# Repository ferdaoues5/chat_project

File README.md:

# Projet ESE  — Robot chat/souris

## Résumé 
Le but du projet est de concevoir un robot capable de se déplacer sur une table (sans tomber de la table), évitant les obstacles, et détectant les autres robots se trouvant sur la table. 
Le robot se trouvant avec d'autres robots sur la table joue soit le rôle de chat ou soit le rôle de souris (jeu du chat et de la souris).

Une liste de composants nous a été imposée.

## 1. Schéma architectural de notre robot

**Liste du matériel**

On utilise le microcontroleur STM32G070RBT6 pour récupérer les données provenants des capteurs, commander les moteurs...

| Capteurs  | Actionneurs | IHM | Horloge |
| ------------- | ------------- | ------------- | ------------- |
| Détection des autres robots : YDLIDAR X4  | 2 Drivers moteurs : ZXBM5210-S | Interrupteur ON/OFF| Quartz 16 MHz |
| Capteurs de bordure (table) : Sharp GP2Y0D805Z0F  | 2 moteurs : DfRobot FIT0520 ou FIT0521 | LEDs indicatives du rôle (chat ou souris)  |  |
| Bumpers (détection de collision)  | | Led de débogage |  |
|Encodeur (pour mesurer vitesse moteur il me semble) | | |  |

## Deadlines

**Entre la toussaint et noel**

- Bibliothèques logicielles
- Drivers
- Organisation du code
- Stratégie et comportements
  
Vacances noel : Samedi 23 décembre au Dimanche 7 janvier  

**Après noel**  
Dernière séance : stratégie et comportements  
TP d’Introduction à la robotique  

**Challenge** le vendredi 12 janvier

Fin du semestre : Samedi 13 janvier  

## Objectifs restants 
**23/11/2023** On a fini le PCB, soudé tous les composants qu'il fallait. Il nous reste maintenant à nous occuper de l'architecture logicielle dans le microcontroleur.
1 niveau d'objectifs au minimum doit être accompli par semaine.

**Niveau 0 :**
Le robot se déplace,
Il ne tombe pas de la table.

**Niveau 1 :**
Il détecte et se dirige vers un objet,
Ou s’en éloigne s’il n’est pas le chat.

**Niveau 2 :**
Il change de comportement (proie/prédateur) après un contact,
Il fonctionne avec plusieurs robots sur la table.

**Niveau 3 :**
Il n’est pas affecté par les obstacles hors de la table,
Il est donc capable de se localiser.

## Problèmes rencontrés

### - Mauvaise liaison du 5V entre la broche du Lidar et un autre point du circuit censé recevoir 5V aussi

__Résolution du problème__ : en soudant un câble entre ces deux points.

### - Pas de capteurs réfléchissants pour la bordure (Sharp GP2Y0D805Z0F)

Il n'y avait plus de capteurs réfléchissants. Heureusement, on nous a suggeré d'utiliser les switchs, et cela est fonctionnel. En fait le robot quand il est sur la table, la languette est près du switch vu que le sol exerce une force vers le haut sur la languette du switch. On a cablé le switch de sorte à ce qu'il soit "normally opened" et donc qu'il transmette une tension que quand la languette s'ouvre.

### - Le contrôle des moteurs
On était tellement tous concentrés sur l'aspect de programmation qu'on en a oublié de tester le bon fonctionnement des composants de notre carte. Résultat, on s'est rendu compte bien trop tard qu'on ne pouvait pas générer de la PWM sur les broches du microcontroleurs reliées aux drivers. Du coup, on ne pouvait seulement contrôler les moteurs en tout ou rien. Il aurait fallu prévoir de mettre une PWM sur Vref des drivers comme ça on aurait été capable de contrôler la vitesse des moteurs dans le cas où la PWM ne serait pas générée pour les entrées du driver. Le problème n'était pas software puisqu'on a réussi à générer de la PWM sur d'autres broches (ex : celle qui était reliée à la broche M_SCTR du LIDAR). On a même essayé de voir à l'oscillo si on avait de la PWM directement sur les broches du STM32. A un moment, une PWM est soudainement apparu sur la broche FWD du driver, puis elle a disparue. 

### - Le Lidar
Un coup, lors du scan, le lidar ne nous donnait pas les 2 octets marquant le début de la trame (0xA55A), un coup il faisait. C'est quelque chose que je ne comprenais. Finalement, le problème venait peut-être du fait d'utiliser l'alimentation continue bleue car bizarrement quand on utilisait la batterie 7.2V NiMH on avait plus de problème de perturbation de la tension et on arrivait à obtenir une trame correcte.

Pas trop de problèmes rencontrés pour la commande health check.

## Au final...

Le robot peut effectivemment "se déplacer" mais comme il le fait à toute vitesse : à cause de son inertie, quand le capteur de bordure lui enverra l'info comme quoi il y a du vide, il tombera dans le vide, même s'il s'arrête.

## Leçons à tirer

- Tester tous les composants et s'assurer de leur bon fonctionnement avant de passer à la partie software
- Mieux communiquer et bien répartir le travail
- Discuter davantage avec d'autres élèves lorsque l'on rencontre des problèmes pour savoir si eux aussi on rencontré les mêmes problèmes

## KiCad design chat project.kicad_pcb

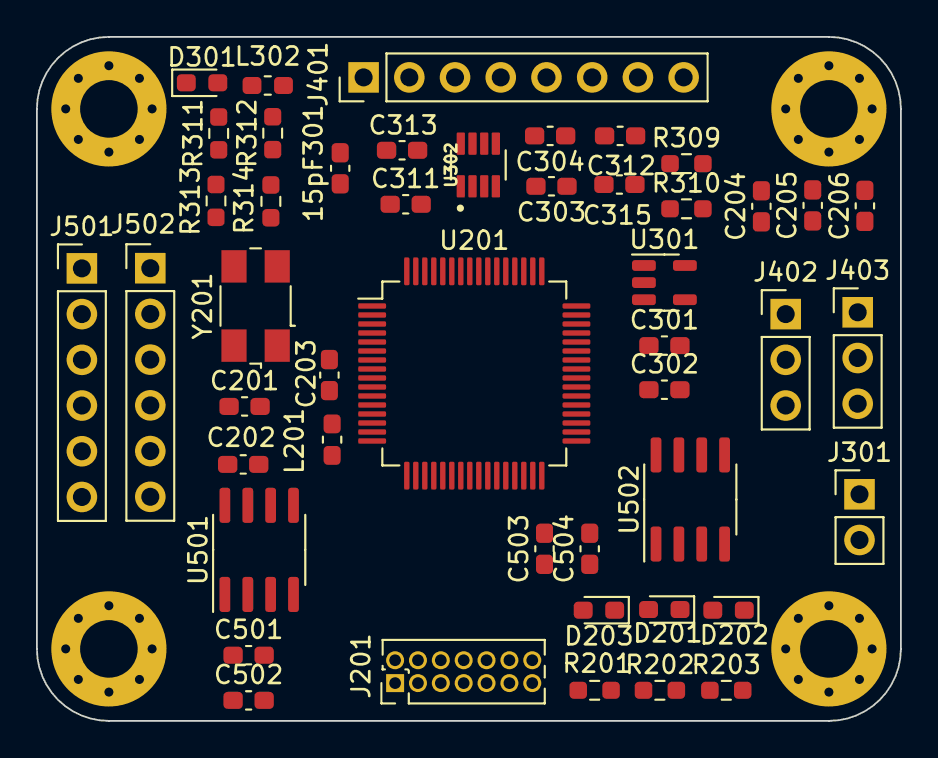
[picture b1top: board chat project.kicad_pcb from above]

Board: 4 copper layers, 48.0 x 38.0 mm, 51 parts (0 on the bottom side), 46 nets, no tracks yet.

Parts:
15pF301: C_Small; C_0603_1608Metric_Pad1.08x0.95mm_HandSolder
C201, C202: 10pF; C_0603_1608Metric_Pad1.08x0.95mm_HandSolder
C203, C301, C302: 1uF; C_0603_1608Metric_Pad1.08x0.95mm_HandSolder
C204, C205: 100nF; C_0603_1608Metric_Pad1.08x0.95mm_HandSolder
C206: 4.7uF; C_0603_1608Metric_Pad1.08x0.95mm_HandSolder
C303, C311, C315: 0.1uF; C_0603_1608Metric_Pad1.08x0.95mm_HandSolder
C304, C312, C313: 22uF; C_0603_1608Metric_Pad1.08x0.95mm_HandSolder
C501, C503: 1µF; C_0603_1608Metric_Pad1.08x0.95mm_HandSolder
C502, C504: 10µF; C_0603_1608Metric_Pad1.08x0.95mm_HandSolder
D201, D202: LED; LED_0603_1608Metric_Pad1.05x0.95mm_HandSolder
D203: RED; LED_0603_1608Metric_Pad1.05x0.95mm_HandSolder
D301: D; D_0603_1608Metric_Pad1.05x0.95mm_HandSolder
H101, H102, H103, H104: MountingHole_Pad; MountingHole_3.2mm_M3_Pad_Via
J201: Conn_02x07_Odd_Even; PinHeader_2x07_P1.27mm_Vertical
J301: Conn_01x02; PinHeader_1x02_P2.54mm_Vertical
J401: Conn_01x08; PinHeader_1x08_P2.54mm_Vertical
J402, J403: Conn_01x03; PinHeader_1x03_P2.54mm_Vertical
J501, J502: Conn_01x06; PinHeader_1x06_P2.54mm_Vertical
L201: 10R; L_0603_1608Metric_Pad1.05x0.95mm_HandSolder
L302: 4.7uH; L_0603_1608Metric_Pad1.05x0.95mm_HandSolder
R201, R202, R203: 1k; R_0603_1608Metric_Pad0.98x0.95mm_HandSolder
R309, R310: 100k; R_0603_1608Metric_Pad0.98x0.95mm_HandSolder
R311: 20k; R_0603_1608Metric_Pad0.98x0.95mm_HandSolder
R312: 16k; R_0603_1608Metric_Pad0.98x0.95mm_HandSolder
R313: 7.68k; R_0603_1608Metric_Pad0.98x0.95mm_HandSolder
R314: 40.2k; R_0603_1608Metric_Pad0.98x0.95mm_HandSolder
U201: STM32G070RBT6; LQFP-64_10x10mm_P0.5mm
U301: MCP1802x-xx02xOT; SOT-23-5
U302: SOT65P280X100-8N
U501, U502: ZXBM5210-S; SOIC-8_3.9x4.9mm_P1.27mm
Y201: 16MHz; Crystal_SMD_0603-4Pin_6.0x3.5mm

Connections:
+3.3V: C204.1, C205.1, C206.1, C302.1, J201.3, J402.1, J403.1, J501.2, J501.5, J502.2, J502.5, U201.8 (VDD/VDDA), U301.5 (VOUT)
+5V: 15pF301.1, C301.1, C312.1, C313.1, J401.8, L302.2, R314.1, U301.1 (VIN), U301.3 (~SHDN)
+7.5V: C501.1, C502.1, C503.1, C504.1, J301.1, U501.2 (VM), U501.3 (VDD), U501.6 (VREF), U502.2 (VM), U502.3 (VDD), U502.6 (VREF)
/Alimentation /VCC: C315.1, D301.2 (A), R309.1, U302.7 (VCC)
Driver1_FWD: U201.36 (PA8), U501.4 (FWD)
Driver1_REV: U201.37 (PA9), U501.5 (REV)
Driver2_FWD: U201.24 (PA7), U502.4 (FWD)
Driver2_REV: U201.23 (PA6), U502.5 (REV)
Encod_A_M1: J501.3, U201.42 (PA10)
Encod_A_M2: J502.3, U201.27 (PB0)
Encod_B_M1: J501.4, U201.43 (PA11)
Encod_B_M2: J502.4, U201.28 (PB1)
GND: C201.1, C202.1, C203.2, C204.2, C205.2, C206.2, C301.2, C302.2, C303.1, C304.1, C312.2, C313.2, C315.2, C501.2, C502.2, C503.2, C504.2, H101.1, H102.1, H103.1, H104.1, J201.5, J201.7, J201.11, J301.2, J401.5, J402.3, J403.3, R201.2, R202.2, R203.2, R313.1, U201.9 (VSS/VSSA), U301.2 (GND), U302.4 (GND), U501.8 (GND), U502.8 (GND), Y201.2, Y201.4
LIDAR_RX: J401.6, U201.20 (PA3)
LIDAR_TX: J401.7, U201.19 (PA2)
Lidar_1: J401.2, U201.52 (PD2)
Lidar_2: J401.3, U201.53 (PD3)
Lidar_PWM: J401.4, U201.51 (PD1)
Motor1_sens1: J501.1, U501.1 (OUT1)
Motor1_sens2: J501.6, U501.7 (OUT2)
Motor2_sens1: J502.1, U502.1 (OUT1)
Motor2_sens2: J502.6, U502.7 (OUT2)
NRST: C203.1, J201.12, U201.12 (NRST)
unnamed: 15pF301.2, R312.2, R313.2, R314.2
unnamed: C202.2, L201.1, Y201.3
unnamed: D201.1 (K), R201.1
unnamed: D202.1 (K), R202.1
unnamed: D203.1 (K), R203.1
unnamed: C311.1, D301.1 (K), R311.2
unnamed: C201.2, U201.10 (PF0-OSC_IN), Y201.1
unnamed: L201.2, U201.11 (PF1-OSC_OUT)
unnamed: R311.1, U302.5 (BST)
unnamed: R310.2, U302.6 (EN/SYNC)
unnamed: R312.1, U302.8 (FB)
unnamed: R309.2, U302.1 (PG)
unnamed: C311.2, L302.1, U302.3 (SW)
SWCLK: J201.6, U201.46 (PA14-BOOT0)
SWDIO: J201.4, U201.45 (PA13)
VCP_RX: J201.14, U201.26 (PC5)
VCP_TX: J201.13, U201.25 (PC4)
VIN: C303.2, C304.2, R310.1, U302.2 (IN)
capt_bordure_1: J402.2, U201.17 (PA0)
capt_bordure_2: J403.2, U201.18 (PA1)
chat_led: D201.2 (A), U201.3 (PC13)
led_de_débogage: D203.2 (A), U201.41 (PD9)
souris_led: D202.2 (A), U201.2 (PC12)

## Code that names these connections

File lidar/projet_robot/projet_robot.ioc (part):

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Mcu.Name=STM32G070RBTx
Mcu.Package=LQFP64
Mcu.UserName=STM32G070RBTx
PA0.GPIOParameters=GPIO_Label
PA0.GPIO_Label=capteur_bord_1
PA0.Signal=GPIO_Input
PA1.GPIOParameters=GPIO_Label
PA1.GPIO_Label=bumper_in3
PA1.Signal=GPIO_Input
PA10.GPIOParameters=GPIO_Label
PA10.GPIO_Label=Driver1_REV
PA10.Signal=S_TIM1_CH3
PA11\ [PA9].GPIOParameters=GPIO_Label
PA11\ [PA9].GPIO_Label=Driver1_FWD
PA11\ [PA9].Signal=S_TIM1_CH4
PA13.Mode=Serial_Wire
PA13.Signal=SYS_SWDIO
PA14-BOOT0.Mode=Serial_Wire
PA14-BOOT0.Signal=SYS_SWCLK
PA2.Mode=Asynchronous
PA2.Signal=USART2_TX
PA3.Mode=Asynchronous
PA3.Signal=USART2_RX
PA6.GPIOParameters=GPIO_Label
PA6.GPIO_Label=Encodeur 2
PA6.Signal=S_TIM3_CH1
PA7.GPIOParameters=GPIO_Label
PA7.GPIO_Label=encoder2_mais_pwm_normale
PA7.Signal=S_TIM3_CH2
PA8.GPIOParameters=GPIO_Label
PA8.GPIO_Label=Encoder 1
PA8.Signal=S_TIM1_CH1
PA9.GPIOParameters=GPIO_Label
PA9.GPIO_Label=Encodeur 1
PA9.Signal=S_TIM1_CH2
PB0.Signal=S_TIM3_CH3
PB1.Signal=S_TIM3_CH4
PB13.GPIOParameters=GPIO_Label
PB13.GPIO_Label=bumper_in4
PB13.Signal=GPIO_Input
PC10.GPIOParameters=GPIO_Label
PC10.GPIO_Label=bumper_in1
PC10.Signal=GPXTI10
PC12.GPIOParameters=GPIO_Label
PC12.GPIO_Label=souris_led
PC12.Signal=GPIO_Output
PC13.GPIOParameters=GPIO_Label
PC13.GPIO_Label=chat_led
PC13.Signal=GPIO_Output
PC3.GPIOParameters=GPIO_Label
PC3.GPIO_Label=bumper_in2
PC3.Signal=GPIO_Input
PC4.GPIOParameters=GPIO_Label
PC4.GPIO_Label=VCP_TX
PC4.Mode=Asynchronous
PC4.Signal=USART1_TX
PC5.GPIOParameters=GPIO_Label
PC5.GPIO_Label=VCP_RX
PC5.Mode=Asynchronous
PC5.Signal=USART1_RX
PD1.GPIOParameters=GPIO_Label
PD1.GPIO_Label=M_SCTR_Lidar
PD1.Signal=S_TIM17_CH1
PD2.GPIOParameters=GPIO_Label
PD2.GPIO_Label=DEV_EN_Lidar
PD2.Signal=GPIO_Output
PD3.GPIOParameters=GPIO_Label
PD3.GPIO_Label=M_EN_Lidar
PD3.Signal=GPIO_Output
PF0-OSC_IN\ (PF0).Mode=HSE-External-Oscillator
PF0-OSC_IN\ (PF0).Signal=RCC_OSC_IN
PF1-OSC_OUT\ (PF1).Mode=HSE-External-Oscillator
PF1-OSC_OUT\ (PF1).Signal=RCC_OSC_OUT
RCC.HSE_VALUE=16000000
RCC.SYSCLKFreq_VALUE=40000000
RCC.SYSCLKSource=RCC_SYSCLKSOURCE_PLLCLK
board=custom

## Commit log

2023-09-19 renamed README
2023-09-24 schéma électrique Version 0
2023-10-08 Add files via upload
    Routage terminé
2023-10-13 Mise à jour PCB
2023-10-25 routage
2023-10-26 fin routage
2024-01-17 ajout fichiers lidar
